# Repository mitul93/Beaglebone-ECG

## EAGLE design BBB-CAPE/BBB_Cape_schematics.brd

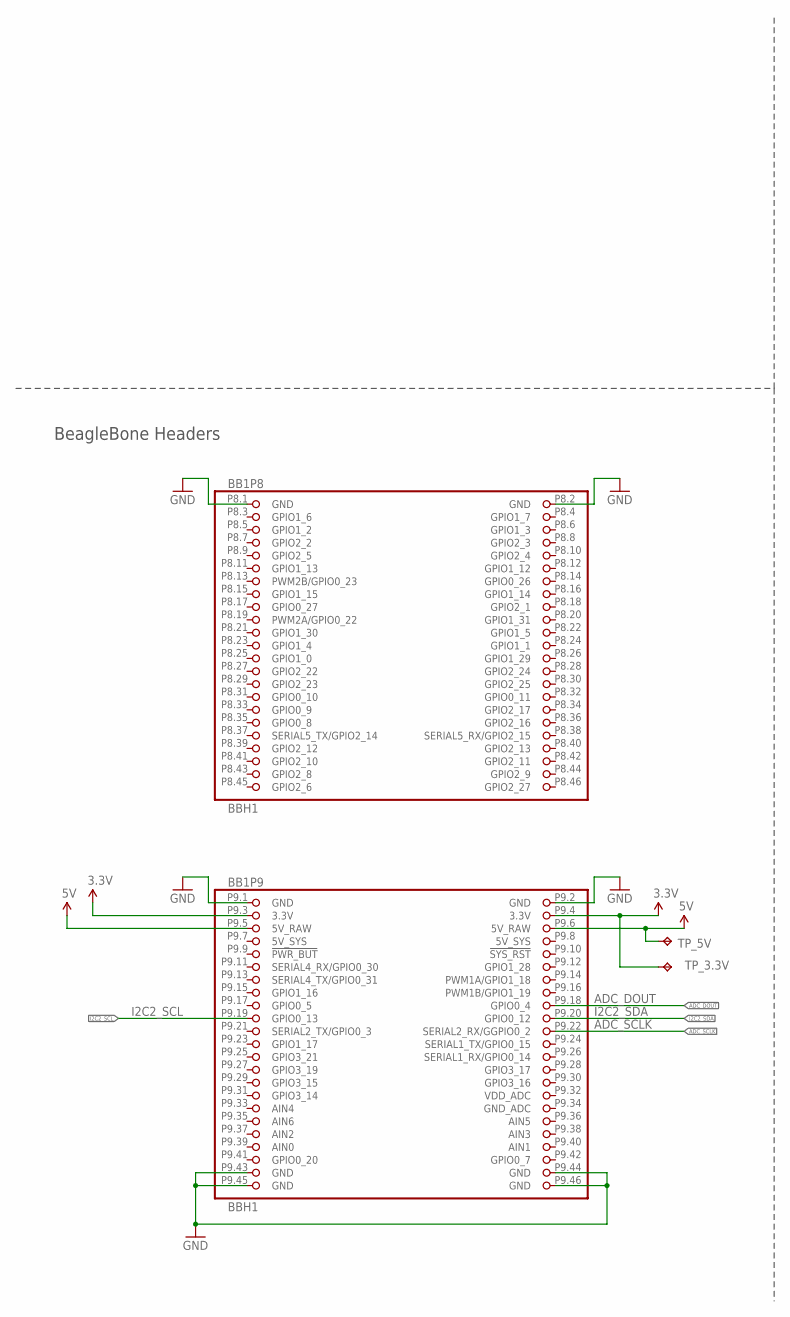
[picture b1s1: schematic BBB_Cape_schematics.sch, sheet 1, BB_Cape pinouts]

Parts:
BB1: BBH1; BB_CAPE
TP_3.3V, TP_5V: TPB2,54; B2,54

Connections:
3.3V: BB1.P9.3 (3.3V), BB1.P9.4 (3.3V), TP_3.3V.TP; also elsewhere on the board
5V: BB1.P9.5 (5V_RAW), BB1.P9.6 (5V_RAW), TP_5V.TP; also elsewhere on the board
5V_SYS: BB1.P9.7 (5V_SYS), BB1.P9.8 (5V_SYS)
ADC_DOUT: BB1.P9.18 (GPIO0_4); also elsewhere on the board
ADC_SCLK: BB1.P9.22 (SERIAL2_RX/GGPIO0_2); also elsewhere on the board
GND: BB1.P8.1 (GND), BB1.P8.2 (GND), BB1.P9.1 (GND), BB1.P9.2 (GND), BB1.P9.43 (GND), BB1.P9.44 (GND), BB1.P9.45 (GND), BB1.P9.46 (GND); also elsewhere on the board
I2C2_SCL: BB1.P9.19 (GPIO0_13)
I2C2_SDA: BB1.P9.20 (GPIO0_12)

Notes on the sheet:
BeagleBone Headers
ADC_SCLK
ADC_DOUT

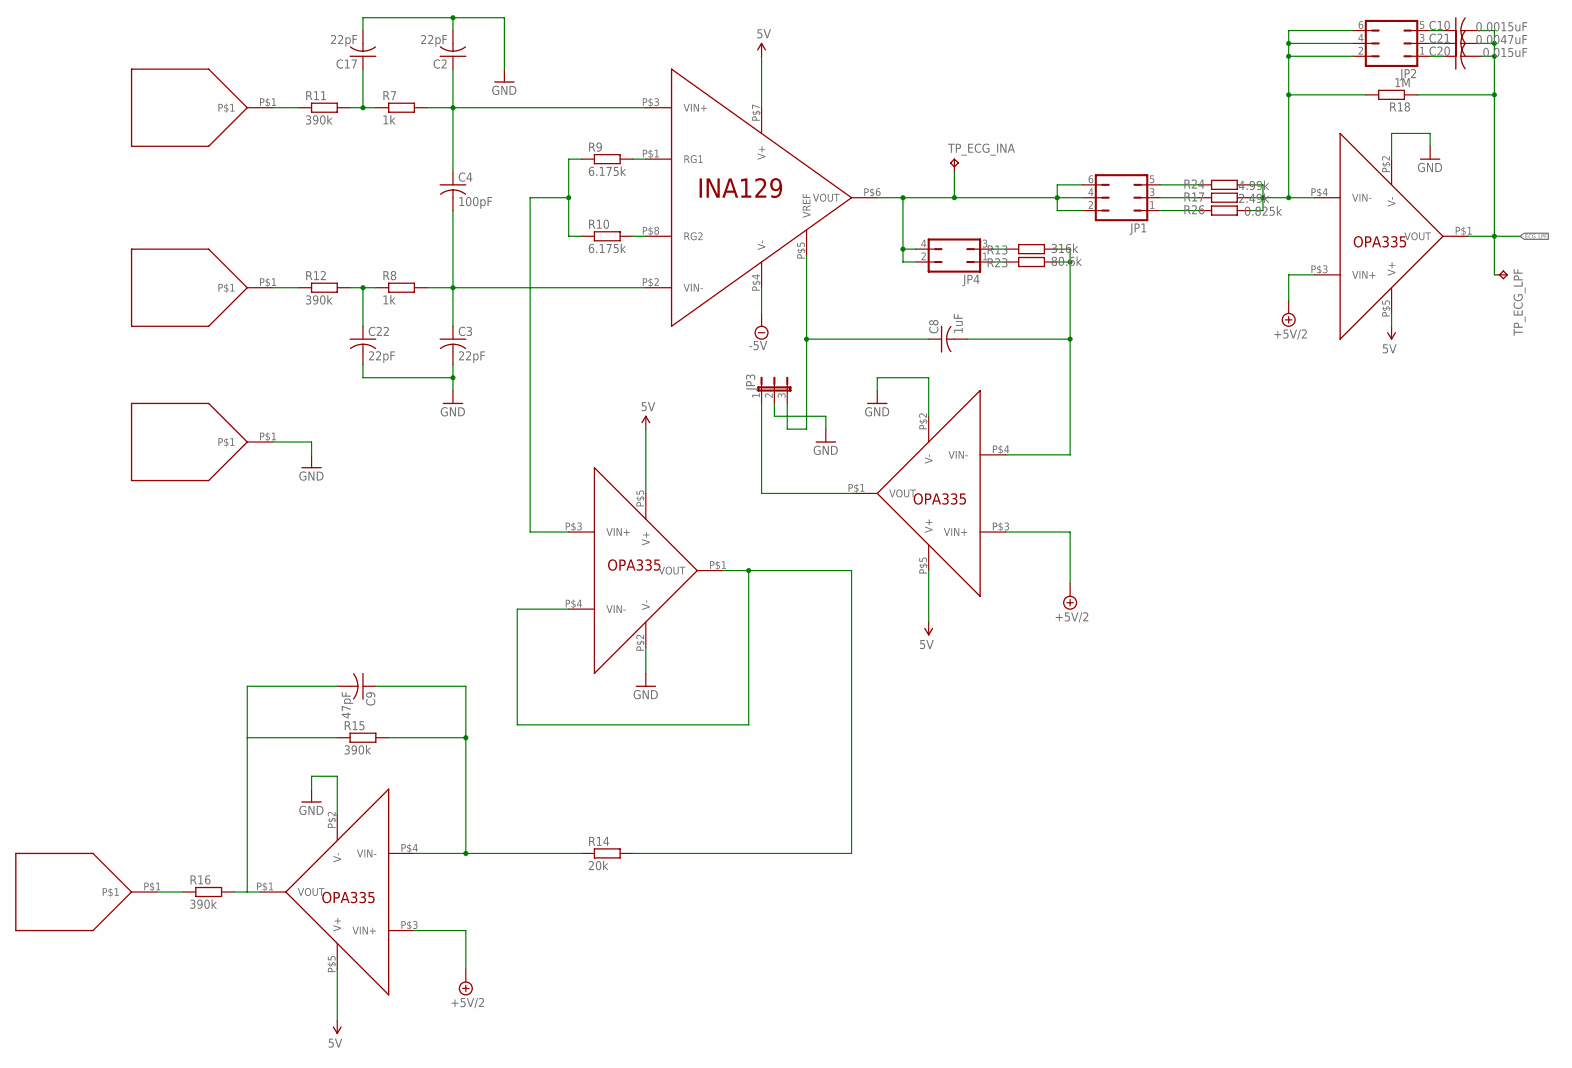
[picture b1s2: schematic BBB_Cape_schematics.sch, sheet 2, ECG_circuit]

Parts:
C2, C3, C17, C22: 22pF; C1206
C4: 100pF; C1206
C8: 1uF; C1206
C9: 47pF; C1206
C10: 0.0015uF; C1206
C20: 0.015uF; C1206
C21: 0.0047uF; C1206
JP1, JP2: JP3Q
JP3: JP2E; JP2
JP4: JP2Q
LH: PAD; RECT_PAD
LH_INDEX: PAD; RECT_PAD
R7, R8: 1k; M1206
R9, R10: 6.175k; M1206
R11, R12, R15, R16: 390k; M1206
R13: 316k; M1206
R14: 20k; M1206
R17: 2.49k; M1206
R18: 1M; M1206
R23: 80.6k; M1206
R24: 4.99k; M1206
R26: 0.825k; M1206
RH: PAD; RECT_PAD
RH_INDEX: PAD; RECT_PAD
TP_ECG_INA: TPB2,54; B2,54
TP_ECG_LPF: TPB2,54; B2,54
U4: INA129
U9, U11, U12, U13: OPA335; SOT23-5

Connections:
5V: U4.P$7 (V+), U9.P$5 (V+), U11.P$5 (V+), U12.P$5 (V+), U13.P$5 (V+); also elsewhere on the board
+5V/2: U9.P$3 (VIN+), U12.P$3 (VIN+), U13.P$3 (VIN+); also elsewhere on the board
-5V: U4.P$4 (V-); also elsewhere on the board
ECG_LPF: C10.2, C20.2, C21.2, R18.1, TP_ECG_LPF.TP, U13.P$1 (VOUT); also elsewhere on the board
GND: C2.2, C3.2, C17.2, C22.2, JP3.2, RH_INDEX.P$1, U9.P$2 (V-), U11.P$2 (V-), U12.P$2 (V-), U13.P$2 (V-); also elsewhere on the board
unnamed: C2.1, C4.1, R7.2, U4.P$3 (VIN+)
unnamed: C3.1, C4.2, R8.2, U4.P$2 (VIN-)
unnamed: R9.2, U4.P$1 (RG1)
unnamed: R10.2, U4.P$8 (RG2)
unnamed: R9.1, R10.1, U11.P$3 (VIN+)
unnamed: C17.1, R7.1, R11.2
unnamed: C22.1, R8.1, R12.2
unnamed: C8.1, JP3.3, U4.P$5 (VREF)
unnamed: JP1.2, JP1.4, JP1.6, JP4.2, JP4.4, TP_ECG_INA.TP, U4.P$6 (VOUT)
unnamed: C8.2, R13.2, R23.2, U9.P$4 (VIN-)
unnamed: R14.2, U11.P$1 (VOUT), U11.P$4 (VIN-)
unnamed: C9.1, R14.1, R15.2, U12.P$4 (VIN-)
unnamed: JP2.2, JP2.4, JP2.6, R17.1, R18.2, R24.1, R26.1, U13.P$4 (VIN-)
unnamed: C9.2, R15.1, R16.2, U12.P$1 (VOUT)
unnamed: LH_INDEX.P$1, R16.1
unnamed: R11.1, RH.P$1
unnamed: LH.P$1, R12.1
unnamed: JP4.3, R13.1
unnamed: JP4.1, R23.1
unnamed: JP3.1, U9.P$1 (VOUT)
unnamed: JP1.5, R24.2
unnamed: JP1.3, R17.2
unnamed: JP1.1, R26.2
unnamed: C10.1, JP2.5
unnamed: C21.1, JP2.3
unnamed: C20.1, JP2.1

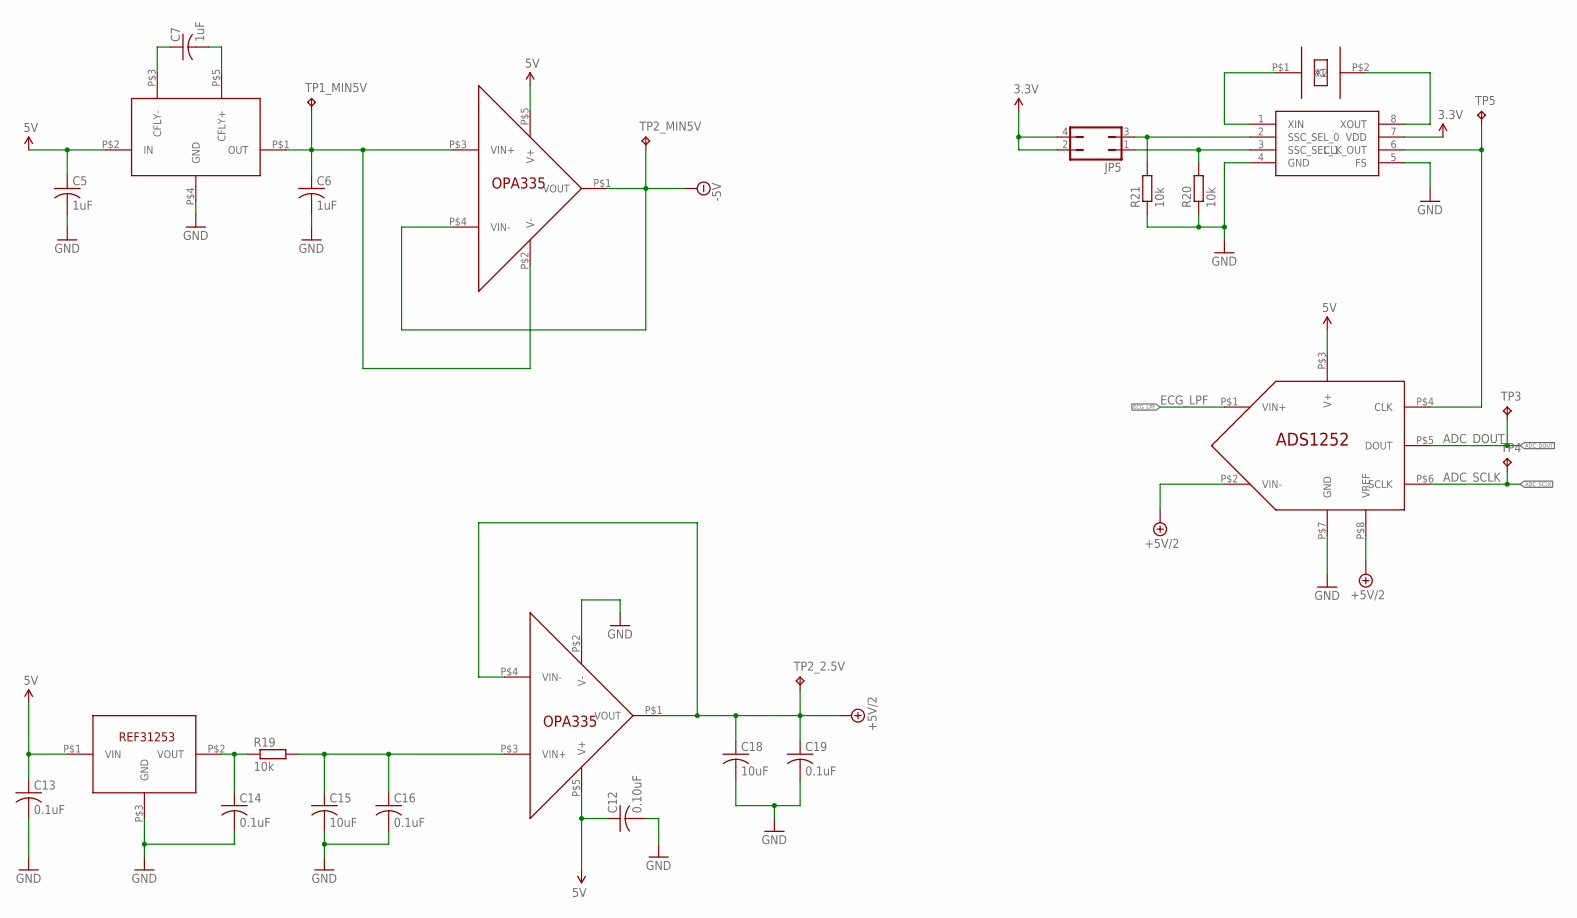
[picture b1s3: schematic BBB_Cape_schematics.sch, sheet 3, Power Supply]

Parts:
C5, C6, C7: 1uF; C1206
C12: 0.10uF; C1206
C13, C14, C16, C19: 0.1uF; C1206
C15, C18: 10uF; C1206
JP5: JP2Q
R19, R20, R21: 10k; M1206
TP1_MIN5V, TP2_2.5V, TP2_MIN5V, TP3, TP4, TP5: TPB2,54; B2,54
U5: TPS60403; SOT23-5
U10: CDCS502; SSOP-8
U14, U22: OPA335; SOT23-5
U19: ADS1252; SOIC-8
U21: REF3125; SOT23-3
U23: ATS16ASM-1; CRYSTAL_SMD

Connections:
3.3V: JP5.2, JP5.4, U10.7 (VDD); also elsewhere on the board
5V: C5.1, C12.1, C13.1, U5.P$2 (IN), U14.P$5 (V+), U19.P$3 (V+), U21.P$1 (VIN), U22.P$5 (V+); also elsewhere on the board
+5V/2: C18.1, C19.1, TP2_2.5V.TP, U19.P$2 (VIN-), U19.P$8 (VREF), U22.P$1 (VOUT), U22.P$4 (VIN-); also elsewhere on the board
-5V: TP2_MIN5V.TP, U14.P$1 (VOUT), U14.P$4 (VIN-); also elsewhere on the board
ADC_DOUT: TP3.TP, U19.P$5 (DOUT); also elsewhere on the board
ADC_SCLK: TP4.TP, U19.P$6 (SCLK); also elsewhere on the board
ECG_LPF: U19.P$1 (VIN+); also elsewhere on the board
GND: C5.2, C6.2, C12.2, C13.2, C14.2, C15.2, C16.2, C18.2, C19.2, R20.1, R21.1, U5.P$4 (GND), U10.4 (GND), U10.5 (FS), U19.P$7 (GND), U21.P$3 (GND), U22.P$2 (V-); also elsewhere on the board
unnamed: C7.2, U5.P$5 (CFLY+)
unnamed: C7.1, U5.P$3 (CFLY-)
unnamed: C6.1, TP1_MIN5V.TP, U5.P$1 (OUT), U14.P$2 (V-), U14.P$3 (VIN+)
unnamed: C14.1, R19.1, U21.P$2 (VOUT)
unnamed: C15.1, C16.1, R19.2, U22.P$3 (VIN+)
unnamed: U10.1 (XIN), U23.P$1 (X1)
unnamed: U10.8 (XOUT), U23.P$2 (X2)
unnamed: TP5.TP, U10.6 (CLK_OUT), U19.P$4 (CLK)
unnamed: JP5.3, R21.2, U10.2 (SSC_SEL_0)
unnamed: JP5.1, R20.2, U10.3 (SSC_SEL_1)

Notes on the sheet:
ECG_LPF
REF31253
ADC_SCLK
ADC_DOUT

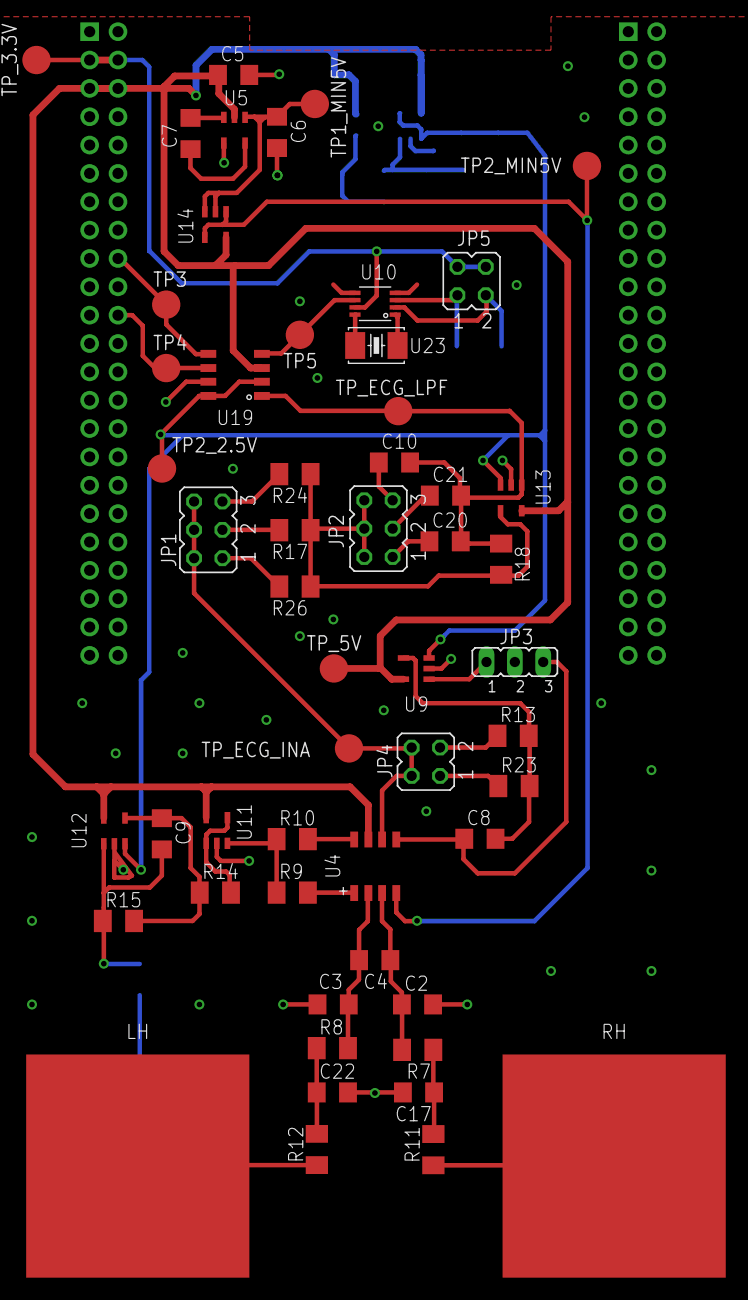
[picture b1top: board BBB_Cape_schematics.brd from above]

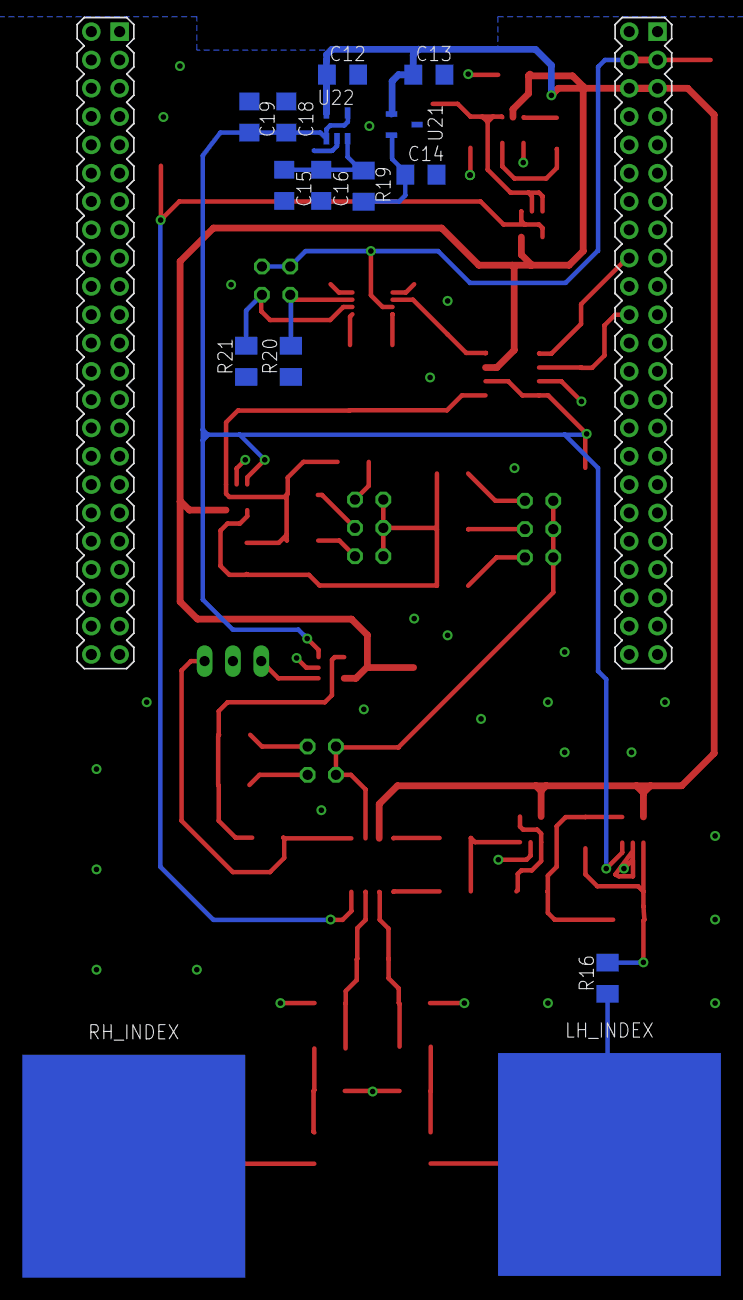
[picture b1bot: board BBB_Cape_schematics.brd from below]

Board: 2 copper layers, 70 parts (15 on the bottom side), 45 nets.

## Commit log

2013-09-21 adding .gitignore and .gitattributes
2013-09-21 Beaglebone cape EAGLE library
2013-09-21 EAGLE library for components used
    The file has library for INA129, LMP2021 and REF5025
2013-09-24 added TMS6040 to component library, changed outline of component symbol from tPlace to tDoc, added INA129, power supply and BB template to schematics
2013-09-25 Added RLD amp, +2.5V Ref and -5V generator circuit
2013-09-29 added device symbol and footprint for finger and thumb PAD
2013-09-29 added device symbol and footprint for ADS1252
2013-09-29 added symbol and footprint for OPA353
2013-09-29 removed REF5025 IC from schematic, instead using REF3125 to generate 2.5V reference voltage
2013-10-01 Add CDCS502 to Components.lbr
2013-10-01 Add ATS16ASM-1 to Components.lbr
2013-10-01 Add Clock ATS16ASM-1 to BBB_Cape_schematics.sch
2013-10-02 Add Resistors to INA129 HPF and LMP2021 LPF for selecting different cut-off frequency; Add DIP Switch in BBB_Cape_schematics.sch
2013-10-07 Add ground pad and remove Dip switch for power in BBB_Cape_schematics.sch
2013-10-09 Add ground pad(for index finger) in BBB_Cape_schematics.sch
2013-10-09 Change layout of Crystal oscillator and rename OPA353 to OPA335 in Components.lbr. Replace OPA2021 with OPA335 in LPF design in BBB_Cape_schematics.sch
2013-10-10 Add signal label and remove warnings by ERC (Electric Rule Check) in BBB_Cape_schematics.sch
2013-10-11 Minor modification of INA129 layout in Components.lbr
2013-10-11 Placement of components in BBB_Cape_schematics.brd, removed ERC erros in BBB_Cape_schematics.sch and Add sign in INA129 to identify pin no 1 in Components.lbr
2013-10-12 Revert "Create new layout file BBB_Cape_schematics.brd". Fresh start of layout.
    This reverts commit bc50a852f2955208c552cd840609eb4807d52a69.
    Conflicts:
    BBB-CAPE/BBB_Cape_schematics.brd
2013-10-12 Add 4D LCD component device symbol and footprint in Components.lbr
2013-10-12 Add 4D LCD to BBB_Cape_schematics.sch
2013-10-12 Add OPA2335 to library in Components.lbr
2013-10-12 Replace all LMP2021 with OPA335 in BBB_Cape_schematics.sch
2013-10-13 Change +5V signal to 5V signal in BBB_Cape_schematics.sch and Update 12MHz crystal package in BBB_Cape_schematics.brd
2013-10-13 Place components and Route for -5V, 2.5V supply in BBB_Cape_schematics.brd and Change +5V to 5V in BBB_schematics.sch
2013-10-14 Solved error caused by imporper node connection across C4 and removed ERC errors in BBB_Cape_schematics.sch
2013-10-14 Connect N$1 with N$20 and N$2 with N$36 in BBB_Cape_schematics.sch
2013-10-14 Revert "Create new layout file BBB_Cape_schematics.brd"
    This reverts commit bc50a852f2955208c552cd840609eb4807d52a69.
    Conflicts:
    BBB-CAPE/BBB_Cape_schematics.brd
2013-10-14 Correct pin connection of U$13 Op-Amp in BBB_Cape_schematics.sch
2013-10-15 Add pin no 1 mark on SOIC-8 and SSOP-8 package in Components.lbr Replace Jumper by Solder jump in BBB_Cape_schematics.sch
2013-10-15 Remove one Resistor from LPF in in BBB_Cape_schematics.sch
2013-10-16 Add >VALUE command in package in Components.lbr
2013-10-16 Route all components in PCB in BBB_Cape_schematics.brd
2013-10-16 Replace solder jump by 0.1 inch header to save space in board in BBB_Cape_schematics.sch
2013-10-19 Modify board boundary, Change orientation of Component names in Silk screen

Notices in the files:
parts and their libraries:
SparkFun-Aesthetics: Licensing: CC v3.0 Share-Alike You are welcome to use this library for commercial purposes.
